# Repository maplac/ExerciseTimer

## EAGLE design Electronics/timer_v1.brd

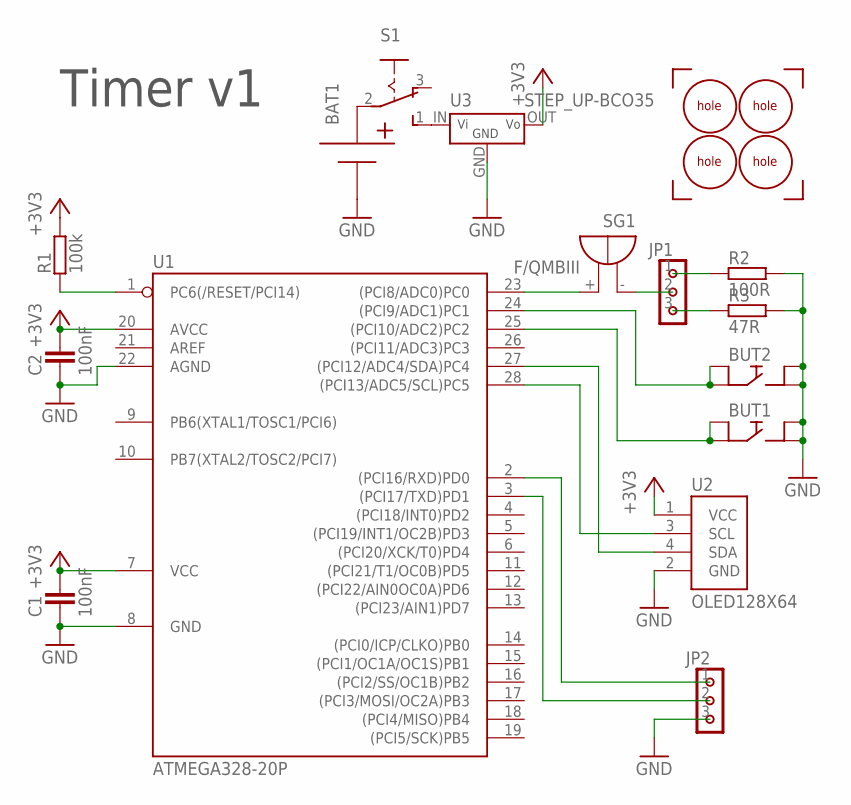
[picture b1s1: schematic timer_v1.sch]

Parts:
BAT1: BATTERY_1X'DOUBLE_SIDE'; 1XAA_BATTERY_HOLDER_2
BUT1, BUT2: BUTTON'THT'; BUTTON
C1, C2: 100nF; C0805
JP1, JP2: PINHD-3X1
R1: 100k; R0805
R2: 100R; R0805
R3: 47R; R0805
S1: 255SB; SLIDE_SWITCH
SG1: F/QMBIII
U1: ATMEGA328-20P; DIL28-3
U2: OLED128X64
U3: STEP_UP-BCO35; BCO35
U$1, U$6, U$7, U$8: CORNER
U$2, U$3, U$4, U$5: HOLE

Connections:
+3V3: C1.2, C2.2, R1.2, U1.7 (VCC), U1.20 (AVCC), U2.1 (VCC), U3.OUT (VOUT)
GND: BAT1.N, BUT1.1, BUT1.3, BUT2.1, BUT2.3, C1.1, C2.1, JP2.3, R2.2, R3.2, U1.8 (GND), U1.22 (AGND), U2.2 (GND), U3.GND
unnamed: BAT1.P, S1.2 (MIDDLE)
unnamed: S1.1 (S), U3.IN (VIN)
unnamed: R1.1, U1.1 (PC6(/RESET/PCI14))
unnamed: U1.27 ((PCI12/ADC4/SDA)PC4), U2.4 (SDA)
unnamed: U1.28 ((PCI13/ADC5/SCL)PC5), U2.3 (SCL)
unnamed: BUT1.2, BUT1.4, U1.25 ((PCI10/ADC2)PC2)
unnamed: BUT2.2, BUT2.4, U1.24 ((PCI9/ADC1)PC1)
unnamed: JP1.2, SG1.- (+)
unnamed: JP1.1, R2.1
unnamed: JP1.3, R3.1
unnamed: SG1.+ (-), U1.23 ((PCI8/ADC0)PC0)
unnamed: JP2.1, U1.2 ((PCI16/RXD)PD0)
unnamed: JP2.2, U1.3 ((PCI17/TXD)PD1)

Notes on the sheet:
Timer v1

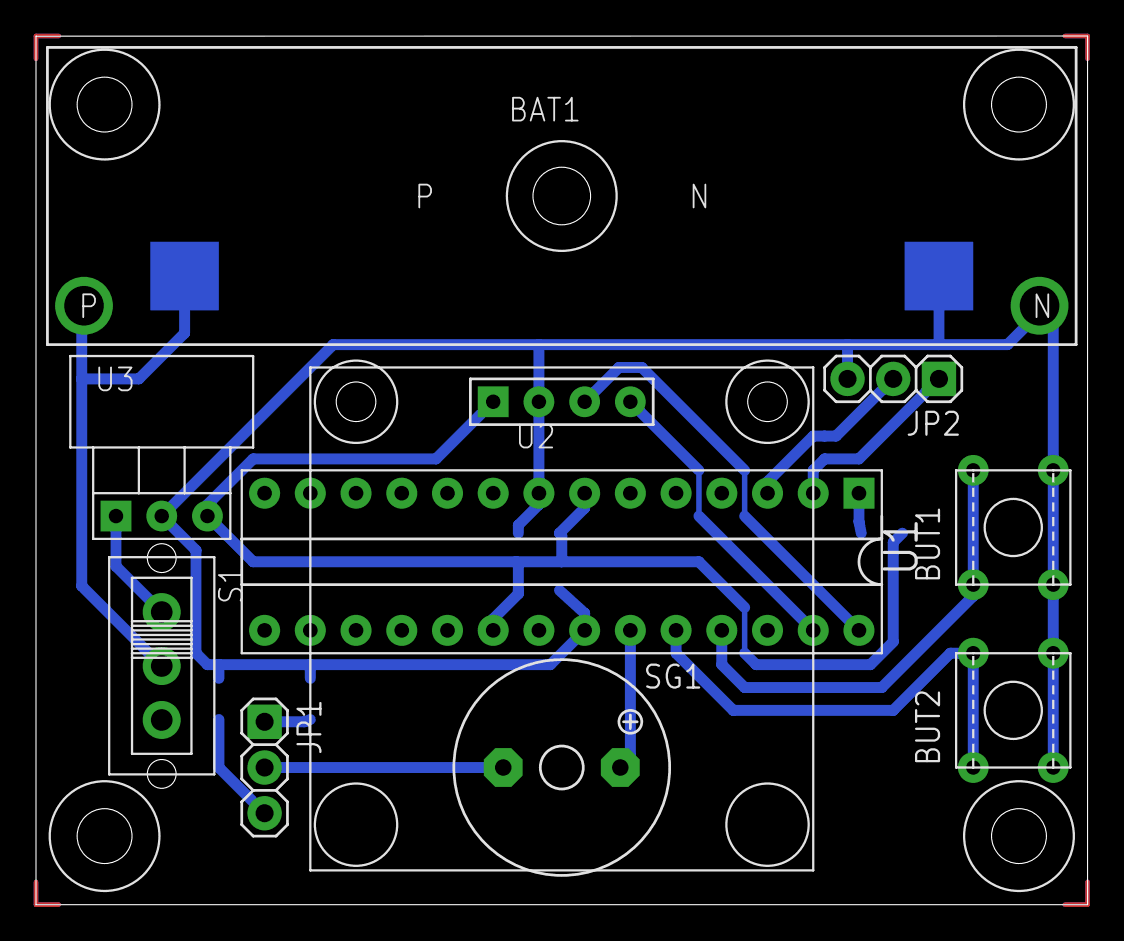
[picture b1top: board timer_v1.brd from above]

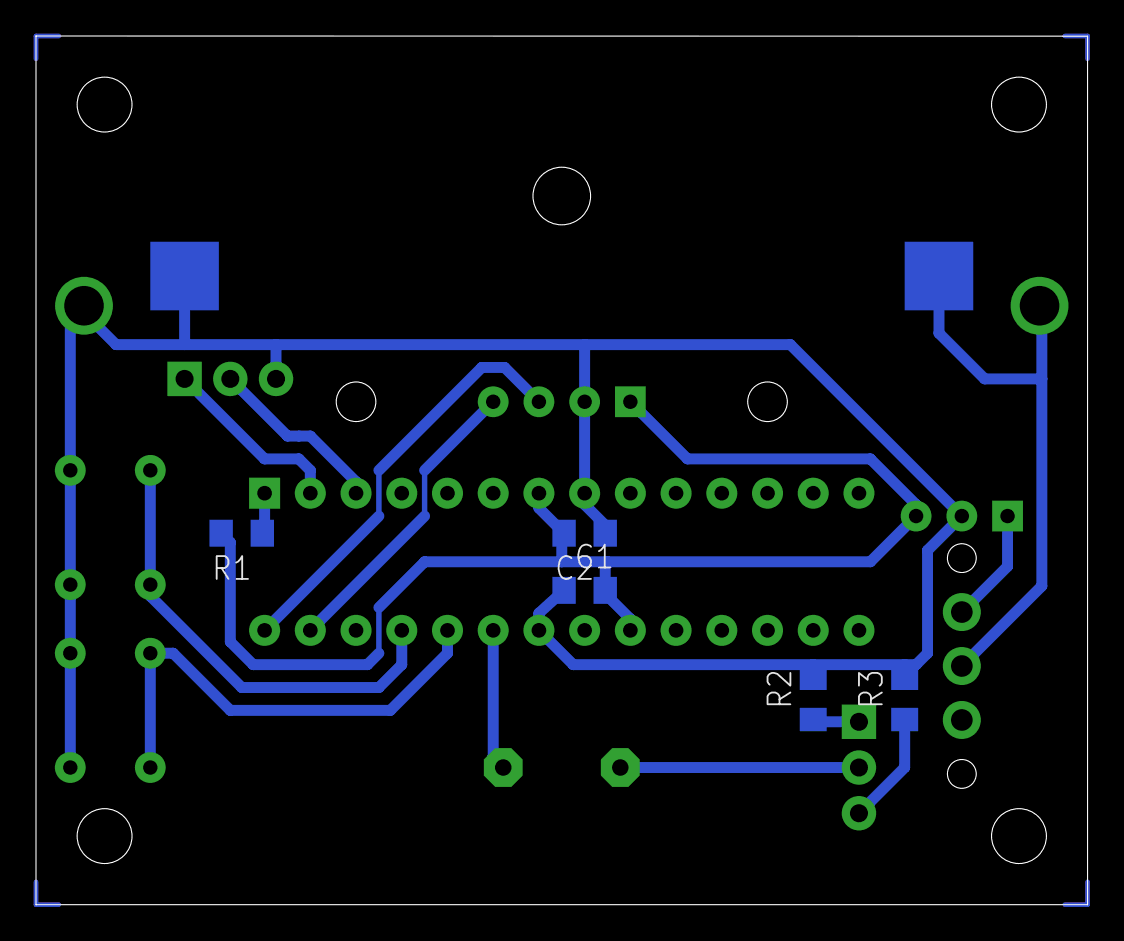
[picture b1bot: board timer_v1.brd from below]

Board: 2 copper layers, 58.4 x 48.3 mm, 23 parts (5 on the bottom side), 15 nets.

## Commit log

2021-03-01 added schematics and PCB
2021-03-01 added firmware
2021-03-01 firmware: added more sounds
